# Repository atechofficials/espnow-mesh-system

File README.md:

# ESPNow Mesh System

A local-first ESP32 smart-home system for **wireless sensing and control**.

This project lets you build a small home mesh using **ESP32-based nodes** and a central **ESP32-S3 gateway**.  
The gateway connects to your Wi-Fi, hosts a browser-based dashboard, can optionally expose its own built-in **SPI room sensor with runtime BMP280/BME280 auto-detection**, communicates with nearby nodes over **ESP-NOW**, can fall back to its own **Offline Mode AP** when your router is unavailable, optionally bridges the system to a local **MQTT broker**, publishes **Home Assistant MQTT auto-discovery**, and uses a companion **ESP32-C3 coprocessor** to handle **gateway-managed Node OTA updates** and future helper tasks.

That means you can:

- monitor room conditions like temperature, humidity, pressure, and light
- use the gateway by itself with an optional built-in room sensor before you add wireless nodes
- control actuator devices like relays from a web dashboard
- mirror supported devices and controls into Home Assistant through MQTT auto-discovery
- pair nodes without entering Wi-Fi credentials on each node
- keep everything running on your own local network

No cloud account. No subscription. No internet dependency for normal use.

---

## What This Project Can Do

### Live monitoring
Open the gateway's IP address in your browser to view live sensor readings from all paired nodes.

### Local control
Turn relays on and off directly from the dashboard.

### Easy pairing
Put a node into pairing mode and the gateway can discover and register it automatically. Fresh, unrenamed nodes now advertise with the last 4 characters of their MAC address appended to the default node name, making it easier to tell identical boards apart before you rename them from the dashboard. The current release line also tightens beacon/discovery timing so pairing candidates appear faster and stale "available to pair" entries clear sooner after a node powers down.

### Node settings from the browser
Change node settings such as:
- Status LED enable/disable
- Relay state persistence
- Sensor-specific options

### Gateway-managed Node OTA
Upload compatible sensor-node, actuator-node, or hybrid-node firmware from the gateway web interface and let the gateway update the selected node without connecting that node to your home Wi-Fi. The gateway now validates both the node role and the node hardware configuration ID before delivery begins.

### Offline gateway access
If your router is unavailable, the gateway can now switch to an **ESP32-S3-hosted Offline Mode AP** so the dashboard stays reachable without internet or home-network access. You can also choose manual offline mode during setup and edit the offline AP credentials later from the dashboard.

### MQTT and Home Assistant
If you enable MQTT in the gateway settings, the gateway publishes **Home Assistant MQTT discovery** for itself, its optional built-in sensor, and supported paired nodes. Relay controls, supported node settings, reboot/unpair actions, and gateway reboot/factory-reset actions can then be used from Home Assistant while staying synchronized with the gateway dashboard.

For temperature reporting, the gateway publishes MQTT temperatures in **degrees Celsius only** for both the built-in sensor and paired sensor nodes. Temperature-unit controls are intentionally **not** exposed to Home Assistant because Home Assistant already handles user-side Celsius/Fahrenheit conversion.

### Automatic recovery
If the gateway or node reboots, the system reconnects automatically and restores state where supported.

---

## Current Project Status

The project already supports **sensor nodes**, **actuator nodes**, and **hybrid nodes**.

### Available right now

| Type | Device | Status |
|------|--------|--------|
| Gateway | ESP32-S3 Gateway | Working |
| Gateway Helper | ESP32-C3 Coprocessor | Working |
| Sensor Node | Envo Mini v1 | Working |
| Actuator Node | ESP32 Relay Node v1 | Working |
| Hybrid Node | ESP32 Hybrid Relay Node v1 | Working |

### Current node capabilities

**Envo Mini v1**
- Temperature
- Atmospheric pressure
- Humidity
- Ambient light

**ESP32 Relay Node v1**
- 4 independent relay outputs
- Relay control from dashboard
- Relay state persistence across reboot
- Status LED setting from dashboard

**ESP32 Hybrid Relay Node v1**
- 4 independent relay outputs
- 4 TTP224 touch inputs
- RC522 RFID card reader support
- RFID card actions that apply saved relay scenes
- Relay control, state sync, and RFID management from the dashboard

### Current MQTT capabilities

- Local MQTT bridge from the gateway to a Mosquitto-compatible broker
- Home Assistant MQTT auto-discovery for:
  - the gateway device
  - optional gateway built-in sensor entities
  - supported sensor, actuator, and hybrid node entities
- Relay and supported setting control from Home Assistant with state sync back to the gateway dashboard
- Gateway reboot and gateway factory reset buttons exposed in Home Assistant
- Graceful retained-topic cleanup during gateway factory reset so the gateway and its connected nodes disappear from Home Assistant cleanly

### Current OTA capabilities

- Gateway self-OTA from the browser with gateway hardware-config ID validation
- Gateway-managed coprocessor OTA from the browser with board-specific coprocessor hardware-config ID validation and progress/error reporting
- Gateway-managed OTA for supported sensor nodes with role and hardware-config ID validation
- Gateway-managed OTA for supported actuator nodes with role and hardware-config ID validation
- Gateway OTA and Node OTA now coordinate helper ownership so the ESP32-C3 coprocessor cannot be reserved by conflicting update flows at the same time
- Gateway self-OTA, coprocessor OTA, and Node OTA remain available while the dashboard is being served through the Offline Mode AP

---

## Why ESP-NOW?

Most DIY smart-home systems put every device directly on Wi-Fi.

This project takes a different approach:

- the **gateway** joins your home Wi-Fi
- the **nodes** talk to the gateway using **ESP-NOW**
- nodes do not need your Wi-Fi password
- pairing is simpler for small embedded devices
- the system stays lightweight and local

This makes the setup especially useful for small ESP32 devices that only need to talk to one central controller.

---

## How It Works

```text
Browser
  |
  | Dashboard
  |
ESP32-S3 Gateway
  |
  | ESP-NOW
  |-- Sensor Nodes
  |-- Actuator Nodes
```

The gateway acts as the bridge between:
- your browser over Wi-Fi
- your MQTT broker / Home Assistant over Wi-Fi
- your ESP32 nodes over ESP-NOW

For **Node OTA**, the gateway temporarily hands firmware delivery to the on-board **ESP32-C3 coprocessor**, which stages the selected node firmware, starts a temporary helper access point, and serves the firmware image to the target node while the main gateway continues managing the mesh and dashboard. Incompatible uploads are blocked up front if the firmware markers do not match the selected node role or hardware configuration. While that helper session is active, the dashboard now blocks conflicting Gateway OTA or coprocessor OTA actions and shows a clear **Coprocessor Busy** state until the helper is free again.

If the gateway loses its router Wi-Fi connection, the **ESP32-S3** can now host an operator-facing Offline Mode AP directly while keeping ESP-NOW active on the last known mesh channel. When the router comes back, the gateway scans for the saved SSID, reconnects automatically, and returns the dashboard to the router-assigned IP.

---

## Hardware Used

### Gateway firmware targets
- ESP32-S3-DevKitC-1-N8R8 for bench development and validation
- Seeed Studio XIAO ESP32-S3 on the new THT gateway carrier variants
- Waveshare ESP32-S3-DevKit-C-N8R8 on the new THT gateway carrier variants

### Gateway helper targets
- ESP32-C3 Super Mini
- Seeed Studio XIAO ESP32-C3
- DFRobot Beetle ESP32-C3

### Gateway reference PCB variants

The current gateway hardware release line now consists of four single-layer, thick-trace, THT-friendly PCB variants intended to be easy to hand-fabricate at home:

| Variant | Main MCU board | Helper MCU board |
|---------|----------------|------------------|
| `ESP32_Mesh_Gateway_v1A` | Seeed Studio XIAO ESP32-S3 | ESP32-C3 Super Mini |
| `ESP32_Mesh_Gateway_v1B` | Seeed Studio XIAO ESP32-S3 | Seeed Studio XIAO ESP32-C3 |
| `ESP32_Mesh_Gateway_v1C` | Seeed Studio XIAO ESP32-S3 | DFRobot Beetle ESP32-C3 |
| `ESP32_Mesh_Gateway_v1D` | Waveshare ESP32-S3-DevKit-C-N8R8 | ESP32-C3 Super Mini |

Shared board-level notes for all four variants:
- All four variants provide solder pads for an optional built-in **BMP280** or **BME280** gateway room sensor module, and the gateway auto-detects which one is attached at boot
- All four variants are intentionally kept on a single copper layer with thick traces for easier home fabrication
- The earlier ESP32-S3 Super Mini based gateway carrier should now be considered deprecated because that board's 4 MB flash is not suitable for the current gateway firmware line, which expects an 8 MB class ESP32-S3 target

### Sensor node reference boards
- DFRobot FireBeetle 2 ESP32-E
- ESP32-C3 Super Mini based **Envo Mini v1** prototype hardware

### Sensor node reference sensors
- BMP280
- DHT22
- TEMT6000

### Actuator node reference board
- ESP32 Dev Module

### Actuator node reference output
- 4-channel active-LOW relay module

### Hybrid node reference add-ons
- TTP224 4-way touch sensor
- RC522 RFID reader module

---

## Quick Start

Board and wiring selection for the current release line are handled through the documented **PlatformIO environments** for each firmware target, with guarded defaults and invalid-define correction in each project's `include/user_config.h`.

### 1. Flash the gateway
Start with the gateway firmware:

[`esp32-gateway/gateway_v1/README.md`](esp32-gateway/gateway_v1/README.md)

For **Node OTA** support, also flash the ESP32-C3 gateway coprocessor once from:

[`esp32-gateway/gateway_v1/coprocessor_esp32c3/`](esp32-gateway/gateway_v1/coprocessor_esp32c3/)

The **Gateway Firmware Update** section in the dashboard can now target either the ESP32-S3 **Main MCU** or the ESP32-C3 **Coprocessor**.

### 2. Flash a node
Choose one:

Sensor node:
[`esp32-nodes/sensor_nodes/envo_mini_v1/README.md`](esp32-nodes/sensor_nodes/envo_mini_v1/README.md)

Actuator node:
[`esp32-nodes/actuator_nodes/esp32_relay_node_v1/README.md`](esp32-nodes/actuator_nodes/esp32_relay_node_v1/README.md)

Hybrid node:
[`esp32-nodes/hybrid_nodes/esp32_hybrid_relay_node_v1/README.md`](esp32-nodes/hybrid_nodes/esp32_hybrid_relay_node_v1/README.md)

### 3. Power on the gateway
On first boot, the gateway opens the setup portal so you can either connect it to your home Wi-Fi or choose manual offline mode with the built-in Offline Mode AP credentials.

### 4. Pair a node
Put a node into pairing mode and let the gateway detect it.

### 5. Open the dashboard
Visit the gateway IP in your browser and start using the system. If the gateway is running in Offline Mode, open:

```text
http://192.168.8.1/
```

### 6. Optional: enable MQTT
If you want Home Assistant integration, open the gateway dashboard, go to the MQTT settings section, enter your broker details, and enable the MQTT bridge. The gateway will publish Home Assistant discovery automatically once it connects to the broker.

---

## Web Dashboard Features

The current dashboard supports:

- viewing all paired nodes
- seeing live sensor readings
- viewing the optional gateway built-in sensor separately from paired-node cards
- controlling relay outputs
- managing Hybrid-node RFID card actions
- opening node settings
- renaming nodes
- rebooting nodes remotely
- updating supported nodes with Node OTA
- updating the gateway main MCU or the ESP32-C3 coprocessor from the **Gateway Firmware Update** section
- disconnecting nodes
- changing gateway settings
- editing built-in gateway sensor temperature-unit / altitude settings when that feature is enabled
- configuring the MQTT bridge and Home Assistant discovery publishing
- editing Offline Mode AP settings and viewing current network mode / access IP
- launching Wi-Fi setup mode
- factory reset options, including a physical long-press reset button on the gateway and graceful node unpairing before the gateway wipes its own state

Home Assistant intentionally does **not** expose:
- relay label settings for actuator or hybrid nodes, because Home Assistant already lets users rename switches and buttons locally
- node or gateway temperature-unit settings, because MQTT temperatures are published in Celsius and Home Assistant handles conversion itself

The dashboard is served directly by the gateway itself.

---

## Who This Project Is For

This project is useful if you are:

### A maker or hobbyist
You want a local smart-home system without cloud dependency.

### A student or learner
You want to explore ESP32 networking, embedded firmware, and browser-based control panels.

### A developer
You want a modular ESP32 project with:
- gateway firmware
- sensor firmware
- actuator firmware
- hybrid node firmware
- a shared protocol
- a live dashboard
- room for future expansion

---

## For Developers

The project is already structured for further development.

If you want to:
- add new sensor nodes
- add new actuator nodes
- add new hybrid nodes
- improve the gateway
- improve the dashboard
- extend the protocol
- contribute fixes or new features

start here:

[`CONTRIBUTING.md`](CONTRIBUTING.md)

More detailed documentation is available in the subproject README files.

---

## Repository Layout

```text
espnow-mesh-system/
|-- README.md
|-- CONTRIBUTING.md
|-- esp32-gateway/
|-- esp32-nodes/
|-- docs/
```

### Main sections

- [`esp32-gateway/`](esp32-gateway/)  
  Gateway documentation and firmware
- [`esp32-gateway/gateway_v1/hardware/`](esp32-gateway/gateway_v1/hardware/)  
  Gateway v1A-v1D PCB resources, schematic PDFs, and development references

- [`esp32-nodes/`](esp32-nodes/)  
  Sensor, actuator, and hybrid node firmware

---

## Documentation Map

If you're just exploring:

- Gateway overview: [`esp32-gateway/README.md`](esp32-gateway/README.md)
- Nodes overview: [`esp32-nodes/README.md`](esp32-nodes/README.md)

If you're building hardware:

- Gateway firmware guide: [`esp32-gateway/gateway_v1/README.md`](esp32-gateway/gateway_v1/README.md)
- Gateway v1A-v1D PCB resources: [`esp32-gateway/gateway_v1/hardware/`](esp32-gateway/gateway_v1/hardware/)
- Sensor node guide: [`esp32-nodes/sensor_nodes/envo_mini_v1/README.md`](esp32-nodes/sensor_nodes/envo_mini_v1/README.md)
- Relay node guide: [`esp32-nodes/actuator_nodes/esp32_relay_node_v1/README.md`](esp32-nodes/actuator_nodes/esp32_relay_node_v1/README.md)
- Hybrid node guide: [`esp32-nodes/hybrid_nodes/esp32_hybrid_relay_node_v1/README.md`](esp32-nodes/hybrid_nodes/esp32_hybrid_relay_node_v1/README.md)
- ESP32-C3 Super Mini WiFi test report: [`docs/esp32_c3_supermini_wifi_tests/README.md`](docs/esp32_c3_supermini_wifi_tests/README.md)

If you're contributing code:

- Contribution guide: [`CONTRIBUTING.md`](CONTRIBUTING.md)

---

## Project Direction

The project currently supports:
- local sensor monitoring
- local relay control
- local RFID-driven relay scenes on Hybrid nodes
- browser-based node management
- gateway-managed Node OTA for supported sensor, actuator, and hybrid nodes with role and hardware-config safety checks
- board-specific configuration cleanup through the new `user_config.h` release line for gateway and node firmware
- ESP32-C3 Super Mini board support with board-gated WiFi transmit power limiting on node firmware where needed

Planned future growth may include:
- more sensor node types
- more actuator node types
- more hybrid sensor + actuator nodes
- improved dashboard views and charts
- cleaner onboarding and flashing experience

---

## License

MIT License

See [`LICENSE`](LICENSE)

---

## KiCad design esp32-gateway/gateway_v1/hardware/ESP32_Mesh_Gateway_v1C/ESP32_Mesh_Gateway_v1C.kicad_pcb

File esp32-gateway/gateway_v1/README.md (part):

# Gateway v1 - Build, Flash, and OTA Guide

Firmware version: **2.6.7**  
Target board: `esp32-s3-devkitc1-n8r8`

Gateway helper coprocessor: **ESP32-C3 firmware v0.3.1**

---

## Highlights in v2.6.7
- Adds clearer built-in sensor probe and diagnosis logging in the gateway serial output
- Auto-detects whether the connected built-in SPI sensor is **BMP280** or **BME280** at runtime and shows data accordingly
- Removes the old manual built-in sensor type selection logic and keeps only a simple built-in sensor enable flag

## Highlights in v2.6.4
- Adds an optional **MQTT bridge** from the gateway to a local broker using `PubSubClient`
- Adds **Home Assistant MQTT auto-discovery** for the gateway, optional gateway built-in sensor, and supported paired sensor/actuator/hybrid nodes
- Keeps supported controls synchronized between Home Assistant and the gateway dashboard
- Exposes **Gateway Reboot** and **Gateway Factory Reset** as Home Assistant MQTT buttons
- Clears retained MQTT discovery/state topics during gateway factory reset so the gateway and its connected nodes disappear cleanly from Home Assistant
- Keeps MQTT temperature publishing in **degrees Celsius only** and intentionally leaves temperature-unit conversion to Home Assistant

## Highlights in v2.5.0
- Adds optional gateway built-in **BMP280/BME280** sensor support on the dedicated gateway PCB header/pads
- Adds a dedicated **Gateway Built-in Sensor** dashboard card plus Settings-page controls for temperature unit and altitude reference
- Keeps the built-in sensor separate from paired-node management and shows a clear Sensor not detected state when the feature is enabled but the hardware is missing or faulty
- Keeps the optional built-in sensor feature board-gated while moving BMP280/BME280 model selection to runtime auto-detection in the newer release line
- Hardens **ESP32-C3 Super Mini** helper AP behavior for Node OTA by applying the documented **8.5 dBm** Wi-Fi TX power cap after Wi-Fi startup and preserving helper-side Wi-Fi stability safeguards
- Refines gateway-side Node OTA status wording so accepted OTA requests report that the gateway is waiting for the node to connect to the helper AP

## Highlights in v2.4.1
- Updates the gateway factory reset flow so all currently paired nodes receive an explicit `UNPAIR_CMD` before the gateway wipes its own state
- Applies this graceful node disconnect behavior to both reset entry points:
  - dashboard **Factory Reset**
  - physical reset button hold sequence
- Prevents previously paired nodes from treating gateway factory reset like a temporary gateway reboot
- Leaves nodes in their expected unpaired / pairing-ready state after factory reset so they can be paired again cleanly
- Uses each node's actual node type in the unpair command path instead of stamping every unpair as `NODE_SENSOR`

## Highlights in v2.4.0
- Adds **Gateway Offline Mode** hosted directly on the ESP32-S3 so the dashboard remains reachable even when the home router is unavailable
- Adds setup-portal controls for choosing **manual Offline Mode** and editing the dedicated Offline Mode AP credentials
- Automatically falls back from router STA mode to the Offline Mode AP when the saved router link is lost
- Automatically scans for the saved router SSID and returns from Offline Mode back to normal router STA mode when that network comes back
- Keeps **Gateway OTA**, **Coprocessor OTA**, and **Node OTA** functional while the gateway is being accessed through the Offline Mode AP
- Adds reconnect-aware dashboard notifications so users are told when the gateway loses the router, switches to Offline Mode, and later returns to router mode
- Adds a runtime **physical factory reset** flow using the board-specific `RESET_BTN_PIN` from `include/user_config.h` instead of relying only on the dashboard action
- Adds a dedicated RGB LED reset sequence for physical factory reset:
  - blinking dark orange while the button is being held
  - solid red once the reset hold threshold is reached
- Increases the physical reset hold time to **6 seconds** for clearer visual confirmation

## Highlights in v2.3.1
- Hardens OTA coordination so **Node OTA**, **Gateway OTA**, and **coprocessor OTA** cannot reserve the ESP32-C3 helper at the same time
- Shows **Coprocessor Busy. Please try after some time.** across the dashboard when the helper is already occupied, including both **Main MCU** and **Coprocessor** targets in the **Gateway Firmware Update** section
- Fixes the Node OTA helper upload-begin target so staged node firmware reaches the coprocessor helper correctly again
- Clears stale Node OTA and coprocessor OTA panel state automatically after backend cleanup so the dashboard returns to idle cleanly

## Highlights in v2.3.0
- Adds **ESP32-C3 coprocessor OTA** support through the **Gateway Firmware Update** section in the web dashboard
- Adds a target selector in the dashboard so the **Gateway Firmware Update** flow can address either the ESP32-S3 **Main MCU** or the ESP32-C3 **Coprocessor**
- Adds board-specific coprocessor firmware validation using the helper board hardware-config ID before UART OTA transfer begins
- Improves OTA error reporting so firmware mismatch messages include the uploaded hardware-config ID clearly in both the serial logs and the web UI
- Adds explicit PlatformIO build environments for the documented gateway hardware combinations and the current custom development combo

## Highlights in v2.2.0
- Polishes discovery timing on both the gateway and node side so pairing candidates appear faster and stale entries clear sooner
- Introduces the `user_config.h` configuration split for cleaner user-tunable firmware definitions
- Documents the current gateway hardware release line around four valid THT-friendly PCB variants (`v1A` to `v1D`)
- Keeps the ESP32-C3 helper workflow aligned with the newer `v0.3.1` coprocessor firmware line

## Highlights in v2.1.4
- Increased the shared node-name field from 16 bytes to 25 bytes (24 visible characters + NUL) for beacon and registration messages, enabling clearer default node names, MAC-suffixed first-boot node names, and longer user-defined names while remaining well within ESP-NOW payload limits

## Highlights in v2.1.3

- Adds a gateway-side **max node capacity** check before a new pairing flow is started
- Shows a dismissible dashboard popup when the user tries to connect another node after the gateway is already full
- Re-shows the capacity warning on repeated over-limit pairing attempts instead of silently failing
- Hardens gateway node-registry restore so temporary low-`MESH_MAX_NODES` test builds do not corrupt runtime memory on boot
- Continues support for the current **ESP32-C3 gateway coprocessor**, Hybrid-node handling, RFID dashboard flow, gateway OTA, and gateway-managed Node OTA

## Highlights in v2.1.2

- Adds the first **ESP32 Mesh System Gateway v1.0A** hardware release to the repository under `hardware/`
- Documents a home-fabrication-friendly gateway PCB built around off-the-shelf **ESP32-S3 Super Mini** and **ESP32-C3 Super Mini** development boards
- Aligns the documented ESP32-S3 <-> ESP32-C3 UART wiring with the new PCB layout:
  - **ESP32-S3 TX GPIO4 -> ESP32-C3 RX GPIO0**
  - **ESP32-S3 RX GPIO5 -> ESP32-C3 TX GPIO1**
- Continues the current gateway OTA, Node OTA, Hybrid-node, and mobile-web-UI feature set from the v2.1.1 release line

## Highlights in v2.1.1

- Continues the **gateway-managed Node OTA** workflow for supported sensor, actuator, and hybrid nodes
- Continues first-class **Hybrid node** handling with capability-aware actuator/RFID synchronization
- Continues support for the **ESP32 Hybrid Relay Node v1** and its RFID card-action workflow in the dashboard
- Adds RFID scan toasts in the dashboard for **new card detection** and **known card action execution**
- Improves the **mobile web UI** with better top-bar responsiveness, mobile sidebar gateway actions, and improved side-nav behavior in portrait and landscape orientations
- Replaces the browser reboot confirmation with a custom **Reboot Gateway** popup consistent with the Factory Reset flow
- Improves popup styling, warning-icon visibility, small-screen landscape fit, and background scroll locking for side menus and dialogs
- Preserves actuator state across gateway reboot so relay cards recover correctly after restart
- Improves gateway OTA success/reboot feedback in the web interface
- Continues support for the **ESP32-C3 gateway coprocessor**, `coproc_ota_protocol.h`, gateway web credentials, relay label assignment, gateway LED control, and schema-driven node settings

---

## Prerequisites

- [PlatformIO Core](https://docs.platformio.org/en/latest/core/installation/index.html) or the PlatformIO IDE extension for VS Code
- USB cable connected to the selected ESP32-S3 gateway main board
- USB cable connected to the selected ESP32-C3 coprocessor board when flashing or debugging the helper firmware

The current hardware release line in `hardware/` instead targets four single-layer carrier-PCB variants built around off-the-shelf ESP32-S3 and ESP32-C3 development boards.

---

## Gateway Hardware Release Line

The current gateway PCB release line documents four valid single-layer, thick-trace, home-fabrication-friendly variants:

| Variant | Main MCU board | Helper MCU board |
|---------|----------------|------------------|
| `ESP32_Mesh_Gateway_v1A` | Seeed Studio XIAO ESP32-S3 | ESP32-C3 Super Mini |
| `ESP32_Mesh_Gateway_v1B` | Seeed Studio XIAO ESP32-S3 | Seeed Studio XIAO ESP32-C3 |
| `ESP32_Mesh_Gateway_v1C` | Seeed Studio XIAO ESP32-S3 | DFRobot Beetle ESP32-C3 |
| `ESP32_Mesh_Gateway_v1D` | Waveshare ESP32-S3-DevKit-C-N8R8 | ESP32-C3 Super Mini |

Shared board-level notes:

- all four variants keep solder pads for an optional **BMP280** or **BME280** gateway-side built-in sensor module
- all four variants are intentionally laid out on a single copper layer with thick traces for easier home fabrication
- the earlier ESP32-S3 Super Mini based gateway carrier should now be treated as deprecated because that board only has 4 MB flash and is not suitable for the current gateway firmware line

The same `hardware/` tree also includes schematic PDFs and a `Development_Resources/` folder with dev-board pinouts and MCU reference documents.

---

## PlatformIO Build Environments

The gateway release line now exposes explicit build environments in `platformio.ini` so users can build the correct firmware for each documented hardware combination without editing board macros manually.

| Environment | Main MCU board | Coprocessor board |
|-------------|----------------|-------------------|
| `gateway_v1a` | Seeed Studio XIAO ESP32-S3 | ESP32-C3 Super Mini |
| `gateway_v1b` | Seeed Studio XIAO ESP32-S3 | Seeed Studio XIAO ESP32-C3 |
| `gateway_v1c` | Seeed Studio XIAO ESP32-S3 | DFRobot Beetle ESP32-C3 |
| `gateway_v1d` | Waveshare ESP32-S3-DevKit-C-N8R8 | ESP32-C3 Super Mini |
| `development` | Espressif ESP32-S3-DevKitC-1-N8R8 | DFRobot Beetle ESP32-C3 |

When building or uploading from USB, select the environment that matches the actual gateway hardware pair you are using.

The current release line keeps the optional gateway built-in sensor feature behind `GATEWAY_BUILTIN_SENSOR_ENABLED`, and the firmware auto-detects whether the attached SPI module is BMP280 or BME280 at runtime.

The newer release line also keeps board and helper selection in PlatformIO build environments while `include/user_config.h` provides guarded defaults and invalid-define correction when no explicit board combination is selected.
## Dependencies

Managed automatically by PlatformIO via `platformio.ini`:

| Library | Version |
|---------|---------|
| WiFiManager | 2.0.17 |
| ESPAsyncWebServer | 3.6.0 |
| AsyncTCP | 3.3.2 |
| ArduinoJson | 7.4.3 |
| Adafruit NeoPixel | 1.15.4 |
| Adafruit Unified Sensor | 1.1.15 |
| Adafruit BMP280 Library | 2.6.8 |
| Adafruit BME280 Library | 2.3.0 |
| PubSubClient | 2.8 |

Framework libraries used directly (no extra install needed): `LittleFS`, `Preferences`, `WiFi`, `esp_now`, `Update`.

---

## Partition Layout

The project now builds against **`partitions_8mb_ota.csv`**.

| Partition | Size |
|-----------|------|
| `nvs` | 20 KB |
| `otadata` | 8 KB |
| `app0` | 1792 KB |
| `app1` | 1792 KB |
| `LittleFS` | 4544 KB |
| `coredump` | 64 KB |

This layout is required for the web-based Gateway OTA update feature and leaves the gateway firmware on an OTA-capable base while the ESP32-C3 helper handles node-firmware delivery.

---

## First-Time Flash / Migration to the OTA-Capable Gateway Line

If you are coming from an older gateway build that used the non-OTA partition table, the **first upgrade to the current OTA-capable gateway line must be done over USB**.

Run these commands from the `gateway_v1/` directory:

```bash
# 1. Erase flash for a clean migration
pio run --target erase

# 2. Upload the LittleFS web assets
pio run --target uploadfs

# 3. Compile and upload the firmware
pio run --target upload
```

After this migration, future **gateway firmware** updates can be done from the web interface.

To use **Node OTA**, also flash the ESP32-C3 helper once from the `coprocessor_esp32c3/` directory:

```bash
cd coprocessor_esp32c3
pio run --target erase
pio run --target upload
pio device monitor
```

See [coprocessor_esp32c3/README.md](coprocessor_esp32c3/README.md) for the helper-specific hardware, transport, and runtime details.

If you change only the dashboard assets later, run:

```bash
pio run --target uploadfs
```

If you change only the firmware later and want to use USB instead of OTA, run:

```bash
pio run --target upload
```

---

## ESP32-C3 Gateway Coprocessor

The Node OTA workflow uses a dedicated **ESP32-C3 coprocessor** connected to the ESP32-S3 gateway.

During a node update, the gateway:

1. validates and stages the uploaded node `firmware.bin`
2. transfers that firmware to the ESP32-C3 helper over UART
3. tells the helper to start a temporary OTA access point
4. instructs the selected node to join that helper AP
5. waits for the node to download, flash, reboot, and re-register

The coprocessor also reports OTA helper status back to the gateway so the web interface can show live progress.

The exact UART routing depends on the selected gateway PCB variant and helper dev board. Keep the helper UART definitions in sync with the intended hardware pair and document any board-specific differences in the hardware release notes when they change.

Shared transport definitions between the gateway and helper live in:

- `include/coproc_ota_protocol.h`
- `coprocessor_esp32c3/include/coproc_ota_protocol.h`

Keep those copies synchronized.

---

## First Boot

1. The gateway tries to reconnect to saved Wi-Fi credentials automatically
2. If no router credentials are stored, WiFiManager opens the setup portal AP:
   - SSID: **`ESP32-Mesh-Gateway`**
   - Password: **`meshsetup`**
3. Connect to that AP from a phone or laptop
4. Open the captive portal and either:
   - select and save your home Wi-Fi network, or
   - enable **Manual Offline Mode** so the gateway boots directly into its dedicated Offline Mode AP
5. After connection to your router, the dashboard becomes available at:

```text
http://<gateway-ip>/
```

6. If the gateway is running in Offline Mode instead, the dashboard becomes available at:

```text
http://192.168.8.1/
```

Wi-Fi credentials, gateway settings, and paired-node records are stored in NVS and survive reboot.

---

## Gateway Offline Mode

The current gateway release line supports a dedicated **Offline Mode AP** hosted on the ESP32-S3 main MCU.

This mode is intended for cases where:

- the gateway has not been given router credentials yet
- the user explicitly enables **Manual Offline Mode** from the setup portal
- the saved home router disappears and the gateway must remain reachable locally

### Offline Mode behavior

- the gateway starts the dedicated Offline Mode AP with its own SSID/password
- the dashboard is served from **`http://192.168.8.1/`**
- paired nodes stay available over ESP-NOW on the last active mesh channel
- the gateway keeps retrying for the saved router SSID in the background
- once the saved router becomes visible again, the gateway automatically returns to normal online router mode

### Configuration

- Offline Mode AP credentials can be changed from the setup portal and later from the dashboard
- setup-portal credentials and Offline Mode AP credentials are stored separately
- router credentials are also mirrored into gateway config storage so reconnect and failover behavior remains reliable across reboot

---

## Gateway Built-in Sensor

The current gateway release line can optionally expose a gateway-side **BMP280** or **BME280** module soldered to the built-in sensor pads on the PCB.

### Configuration

- the built-in sensor feature is enabled or disabled with `GATEWAY_BUILTIN_SENSOR_ENABLED`
- when enabled, the gateway probes the attached SPI module at boot and auto-detects whether it is a BMP280 or BME280
- the gateway reuses the board-specific SPI pin mapping defined in `user_config.h` and prints clearer serial probe diagnostics when detection succeeds or fails

### Dashboard and Settings behavior

- the dashboard shows a dedicated **Gateway Built-in Sensor** card instead of treating the sensor like a paired node
- temperature and sea-level-corrected pressure are shown for both detected BMP280 and BME280 modules
- the built-in sensor status badge reflects the detected model (`BMP280` or `BME280`)
- humidity is shown only when the detected module is BME280
- the Settings page exposes temperature-unit and altitude-reference controls for the built-in sensor
- if the feature is enabled in firmware but the module is missing or faulty, the dashboard and Settings page remain visible and report **Sensor not detected**
- the MQTT / Home Assistant bridge publishes gateway built-in temperature in **degrees Celsius only** and does not expose the built-in sensor temperature-unit setting, because Home Assistant already handles unit conversion on its own side

---

## MQTT and Home Assistant Integration

The current gateway release line can optionally bridge the local ESP-NOW system into a Mosquitto-compatible MQTT broker.

When MQTT is enabled from the dashboard:

- the gateway publishes Home Assistant MQTT discovery automatically
- the gateway itself appears as a Home Assistant device
- supported paired nodes appear under the same gateway-managed device hierarchy
- relay controls, supported node settings, reboot actions, and unpair actions can be triggered from Home Assistant
- gateway reboot and factory reset can also be triggered from Home Assistant

Intentional Home Assistant behavior:

- relay label settings are **not** exposed, because Home Assistant already lets users rename switches/buttons locally
- temperature-unit settings are **not** exposed for the gateway built-in sensor or paired sensor nodes
- MQTT temperatures are published in **degrees Celsius** only, and Home Assistant handles conversion to Fahrenheit if the user selects that display unit

During gateway factory reset, the firmware now clears retained MQTT discovery/state topics before rebooting so the gateway and its connected nodes disappear from Home Assistant cleanly instead of leaving stale devices behind.

---

## Gateway OTA Update from the Web Interface

Once an OTA-capable gateway build is already installed, the gateway can update its **own firmware** directly from the dashboard.

This flow remains available when the dashboard is being served either from the normal router connection or from the ESP32-S3 Offline Mode AP.

### Steps

1. Build a new gateway firmware binary:

```bash
pio run
```

2. Open the dashboard in a browser
3. Go to **Settings -> Gateway Firmware Update**
4. Select the new `firmware.bin`
5. Click **Upload Gateway Firmware**
6. Confirm the update when prompted

The **Gateway Firmware Update** panel now includes a target selector with **Main MCU** and **Coprocessor** options. The steps in this section cover the ESP32-S3 main-firmware path.
### What the gateway does

- validates the uploaded image
- validates the uploaded gateway hardware configuration marker (`GWHWCFG`)
- checks OTA slot size and image type
- flashes the inactive OTA slot
- reports progress/errors in the web UI
- reboots into the new firmware automatically on success

### Notes

- Upload **`firmware.bin`**, not `bootloader.bin`, not `partitions.bin`
- If the web UI assets were changed, also upload LittleFS via `pio run --target uploadfs`
- The current release line moves user-facing configuration definitions into `user_config.h`; older checkouts may still have some of the same knobs in `src/main.cpp`

---

## Gateway Coprocessor OTA Update from the Web Interface

The same **Gateway Firmware Update** panel can now also update the attached **ESP32-C3 coprocessor** from the browser.

This flow also remains available while the gateway is operating in Offline Mode.

### Steps

1. Build the matching coprocessor helper firmware binary from `coprocessor_esp32c3/` using the correct environment for your helper board
2. Open the dashboard in a browser
3. Go to **Settings -> Gateway Firmware Update**
4. Select **Coprocessor** from the MCU target dropdown
5. Select the helper `firmware.bin`
6. Click **Upload Gateway Firmware**

### What the gateway does

- validates the uploaded ESP32 application image
- validates the uploaded coprocessor hardware-config marker against the expected helper board type
- checks that the image fits in the coprocessor OTA slot
- stages the firmware in LittleFS
- asks the helper to halt normal work and prepare for self-OTA
- transfers the firmware to the ESP32-C3 over UART
- waits for the helper to flash, reboot, and reconnect
- reports progress and errors back to the web UI

### Notes

- Upload the helper `firmware.bin` from the environment matching your helper board: `beetle_esp32c3`, `xiao_esp32c3`, or `esp32c3_sm`
- Wrong-board helper uploads are rejected before UART transfer begins
- If the ESP32-C3 is already serving as the Node OTA helper, the **Gateway Firmware Update** section now blocks both MCU targets and shows a shared **Coprocessor Busy** message until the helper is released
## Node OTA Update from the Web Interface

The gateway can also update a paired **sensor node**, **actuator node**, or **hybrid node** from the dashboard.

This flow remains available in both normal router mode and the ESP32-S3 Offline Mode AP.

### Supported flow

1. Build the target node firmware and locate its `firmware.bin`
2. Open the dashboard in a browser
3. Go to the **Node OTA Update** section
4. Select the target node and upload the matching node `firmware.bin`
5. Wait for the gateway to stage the file, arm the ESP32-C3 helper, and start the temporary helper AP
6. The target node downloads the staged image, flashes it, reboots, and re-registers automatically

### What the gateway checks

- uploaded image role matches the selected node type (`SENSOR`, `ACTUATOR`, or `HYBRID`)
- uploaded node hardware configuration marker matches the selected node's reported `HW_CONFIG_ID`
- firmware metadata is readable before starting delivery
- helper staging finishes successfully on the ESP32-C3
- the node accepts OTA mode and reconnects after reboot

### Notes

- Upload **node `firmware.bin`** from the node project, not bootloader or partition files
- The node does **not** need your home Wi-Fi credentials; it only joins the temporary helper AP for the OTA window
- If the coprocessor is already busy with a helper self-update, the **Node OTA Update** section disables its controls and shows the shared **Coprocessor Busy** message until the helper is available again
- Supported and verified flows now include same-version reflashing, upgrades, downgrades, sensor-node OTA, relay-node OTA, hybrid-node OTA, and node OTA after gateway reboot

---

## Updating the Setup Portal AP Credentials

The WiFiManager setup-portal SSID and password can be changed from the dashboard without reflashing:

1. Open **Settings -> Gateway Network**
2. Edit the setup AP SSID and/or password
3. Click **Save AP Config**

These values are used the next time the gateway has to open the setup portal.

---

## Web Interface Access Control

The dashboard can be left open or protected with username/password credentials from the web interface.

### Stored in NVS

- web username
- password hash
- remember token

If credentials are forgotten, recover access by performing a **factory reset**.

---

## Factory Reset

Hold the dedicated **physical factory reset button** connected to the currently selected `RESET_BTN_PIN` in `include/user_config.h` for **6 seconds** while the gateway is running, or trigger **Factory Reset** from the dashboard.

The exact MCU pin is **board-dependent** and may differ between gateway hardware variants and build environments, so do not assume a universal reset-button pin across all gateway boards.

During a physical reset hold, the gateway RGB LED shows:

- **blinking dark orange** while the reset hold is in progress
- **solid red** once the hold threshold has been reached and reset is about to trigger

If the button is released early, the reset is canceled and LED ownership returns to the previous runtime state.

The physical reset LED sequence is always shown, even if the user has disabled the normal Gateway Status LED from the dashboard.

Before the gateway wipes its own registry and saved credentials, it now sends a graceful unpair/disconnect command to every currently paired node. This allows those nodes to clear their saved gateway binding and return to pairing mode instead of briefly behaving as though the gateway only rebooted temporarily.

This clears:

- saved Wi-Fi / router credentials
- custom setup AP credentials
- custom Offline Mode AP credentials
- web interface credentials
- paired node registry
- saved relay label assignments

The gateway then reboots and returns to setup mode.

---

## Key Configuration (`include/user_config.h`)

The current release line keeps board selection, pin definitions, and user-facing firmware defaults in `include/user_config.h` so `main.cpp` can stay focused on runtime logic. Older checkouts may still keep some of the same constants in `src/main.cpp`.

The newer `v2.4.1` line also keeps the setup-portal defaults, Offline Mode defaults, board-specific reset-button wiring through `RESET_BTN_PIN`, and gateway LED ownership behavior aligned through `user_config.h`.

| Constant | Default | Description |
|----------|---------|-------------|
| `AP_SSID_DEFAULT` | `"ESP32-Mesh-Gateway"` | WiFiManager setup portal SSID |
| `AP_PASS_DEFAULT` | `"meshsetup"` | WiFiManager setup portal password |
| `WEB_PORT` | `80` | HTTP/WebSocket port |
| `WS_UPDATE_MS` | `2000` | Node/discovery push interval to browser |
| `WS_META_MS` | `10000` | Gateway meta push interval to browser |
| `RX_QUEUE_SIZE` | `30` | Incoming ESP-NOW packet queue depth |
| `GW_LED_PIN` | `38` | On-board WS2812B gateway status LED |

Timing constants shared with the nodes live in `include/mesh_protocol.h`.

Node OTA transport and helper constants are shared with the ESP32-C3 helper through `include/coproc_ota_protocol.h`.

Use `user_config.h` for board-specific pin mappings, helper UART routing, and other user-tunable firmware selections in the newer release line.

If you are working against one of the gateway PCB variants instead of the original dev-kit wiring, keep the UART pin assignments and helper-board assumptions aligned with the specific hardware variant you are building.

---

## Serial Monitor

```bash
pio device monitor
```

Default baud rate: **115200**

Useful log prefixes:

| Prefix | Meaning |
|--------|---------|
| `[BOOT]` | Startup sequence |
| `[FS]` | LittleFS mount / file listing |
| `[WiFi]` | Wi-Fi connection events |
| `[ESP-NOW]` | ESP-NOW init and TX callbacks |
| `[DISC]` | Node discovery |
| `[PAIR]` | Pairing handshake |
| `[MESH]` | Node registration, relay/actuator state, reconnects |
| `[CFG]` | Gateway or node configuration activity |
| `[AUTH]` | Web interface authentication |
| `[WS]` | WebSocket client activity |
| `[OTA]` | Gateway OTA upload and reboot flow |
| `[C3]` | ESP32-C3 helper handshake, staging, and helper status |
| `[NODE OTA]` | Node OTA job lifecycle, node reconnect detection, and completion |

---

## WebSocket Message Reference

The dashboard communicates with the gateway over a single WebSocket at:

```text
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
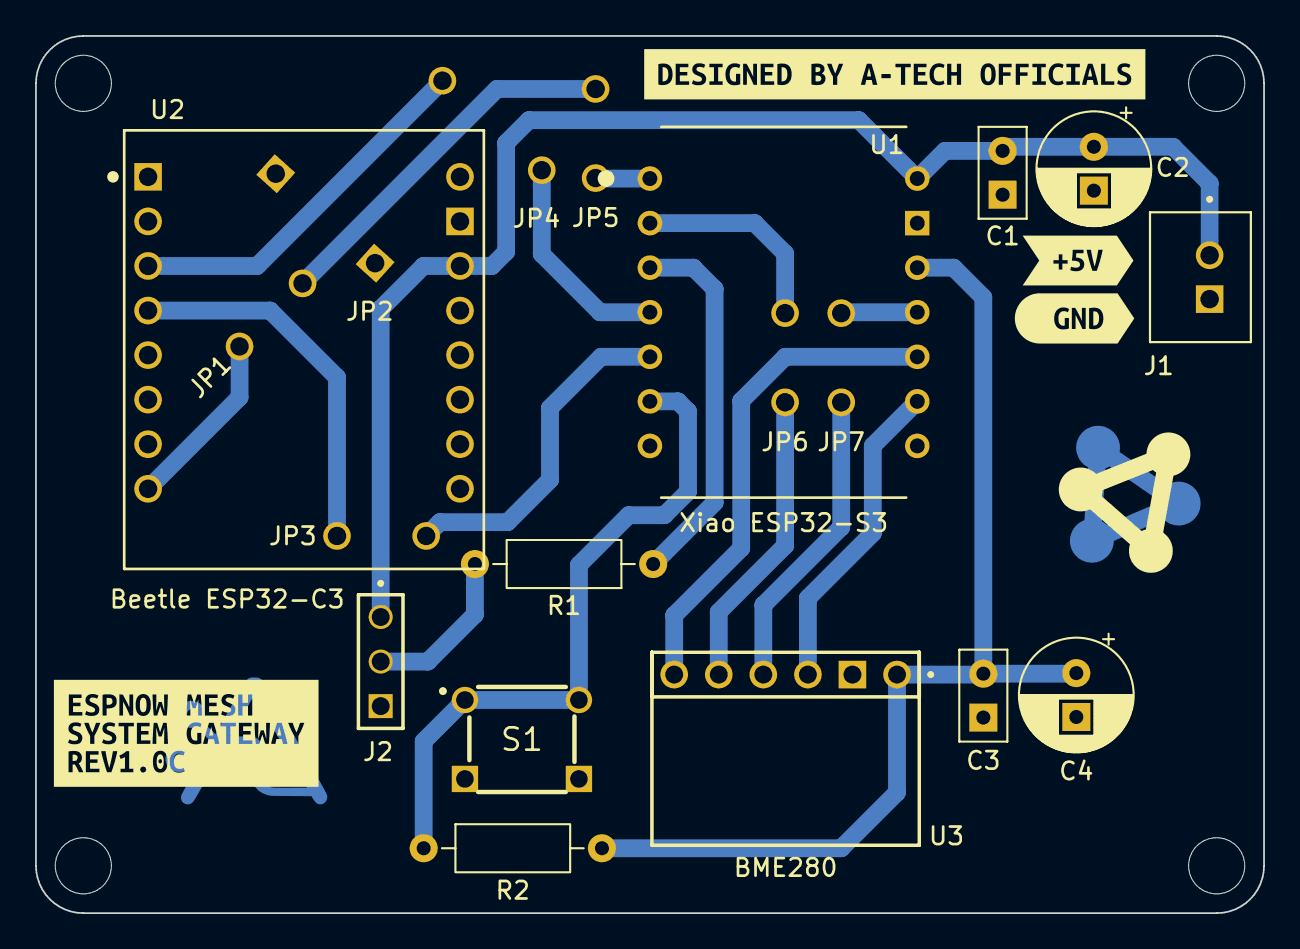
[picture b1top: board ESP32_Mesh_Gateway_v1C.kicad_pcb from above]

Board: 2 copper layers, 70.0 x 50.0 mm, 27 parts (0 on the bottom side), 13 nets.

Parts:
C1, C3: 100nF; C_Disc_D5.0mm_W2.5mm_P2.50mm
C2, C4: 100uF; CP_Radial_D6.3mm_P2.50mm
H1, H2, H3, H4: MountingHole; MountingHole_3.2mm_M3_DIN965
J1: Ext Power; B2B-XH-A__LF__SN_
J2: RGB LED; SAMTEC_TSW-103-07-G-S
JP1, JP3, JP5, JP6, JP7: 2H_Jumper_P5.08mm; 2H_Jumper_P5.08
JP2, JP4: 2H_Jumper_P7.62mm
R1: 100R; R_Axial_DIN0207_L6.3mm_D2.5mm_P10.16mm_Horizontal
R2: 10K; R_Axial_DIN0207_L6.3mm_D2.5mm_P10.16mm_Horizontal
S1: RST BTN; FSM4JH
U1: XIAO-ESP32-S3-DIP; Xiao ESP32-S3 THT
U2: DFRobot Beetle ESP32-C3; DFRobot_Beetle_ESP32-C3
U3: BME280; BME280_Module
kibuzzard-69C035C1: G***; kibuzzard-69C035C1
kibuzzard-69C036F1: G***; kibuzzard-69C036F1
kibuzzard-69C03701: G***; kibuzzard-69C03701
kibuzzard-69CC23E0: G***; kibuzzard-69CC23E0

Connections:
+3.3V: C3.1, C4.1, R2.2, U1.12 (3V3), U3.06
+5V: C1.1, C2.1, J1.1, J2.01, U1.14 (VBUS), U2.14 (VIN)
ARGB_LED: R1.1, U1.3 (GPIO3_A2_D2)
BMP_CS: JP6.1, JP6.2, U1.2 (GPIO2_A1_D1), U3.02
FR_BTN: R2.1, S1.1, S1.2, U1.6 (GPIO6_A5_D5_SCL)
GND: C1.2, C2.2, C3.2, C4.2, J1.2, J2.03, JP2.1, JP2.2, S1.3, S1.4, U1.13 (GND), U2.1 (GND), U2.15 (GND), U3.05
HELPER_RST: JP1.1, JP1.2, JP5.1, JP5.2, U1.1 (GPIO1_A0_D0), U2.8 (GPIO7/SS)
MISO: U1.10 (GPIO8_A9_D9_MISO), U3.01
MOSI: JP7.1, JP7.2, U1.11 (GPIO9_A10_D10_MOSI), U3.03
unnamed: J2.02, R1.2
RXD0: JP3.1, JP3.2, U1.5 (GPIO5_A4_D4_SDA), U2.4 (GPIO1/ADC1)
RXD1: JP4.1, JP4.2, U1.4 (GPIO4_A3_D3), U2.3 (GPIO0/ADC0)
SCK: U1.9 (GPIO7_A8_D8_SCK), U3.04

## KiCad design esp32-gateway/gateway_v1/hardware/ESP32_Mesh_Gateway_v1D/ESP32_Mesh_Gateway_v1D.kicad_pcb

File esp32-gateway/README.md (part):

# ESP32 Gateway

The gateway is the heart of the ESPNow Mesh System. It runs on an **ESP32-S3** and bridges your Wi-Fi network with the ESP-NOW mesh while serving a live web dashboard, managing paired nodes, optionally exposing a built-in **SPI room sensor with runtime BMP280/BME280 auto-detection**, supporting a local **MQTT bridge** with **Home Assistant MQTT auto-discovery**, supporting **web-based gateway OTA firmware updates**, coordinating **gateway-managed Node OTA updates** for sensor, actuator, and hybrid nodes with a companion **ESP32-C3 coprocessor**, and providing an **Offline Mode AP** so the dashboard stays reachable even when your home router is unavailable.

---

## Hardware

| Item | Detail |
|------|--------|
| Main Board | ESP32-S3-DevKitC-1-N8R8 |
| Companion Helper | ESP32-C3 coprocessor for Node OTA and future helper tasks |
| Flash | 8 MB (Quad) |
| PSRAM | 8 MB (Octal) |
| Status LED | WS2812B on GPIO 38 (on-board) |
| Factory reset button | Board-dependent and configured by `RESET_BTN_PIN` in `gateway_v1/include/user_config.h` |

The current gateway hardware release line now tracks four single-layer, thick-trace, THT-friendly PCB variants under `gateway_v1/hardware/`:

| Variant | Main MCU board | Helper MCU board |
|---------|----------------|------------------|
| `ESP32_Mesh_Gateway_v1A` | Seeed Studio XIAO ESP32-S3 | ESP32-C3 Super Mini |
| `ESP32_Mesh_Gateway_v1B` | Seeed Studio XIAO ESP32-S3 | Seeed Studio XIAO ESP32-C3 |
| `ESP32_Mesh_Gateway_v1C` | Seeed Studio XIAO ESP32-S3 | DFRobot Beetle ESP32-C3 |
| `ESP32_Mesh_Gateway_v1D` | Waveshare ESP32-S3-DevKit-C-N8R8 | ESP32-C3 Super Mini |

All four variants include solder pads for an optional built-in **BMP280** or **BME280** gateway-side room sensor, and the gateway now auto-detects the attached sensor model at runtime. The older ESP32-S3 Super Mini based carrier should now be treated as deprecated because the current gateway firmware line expects an 8 MB class ESP32-S3 target.

---

## Responsibilities

- Connects to your home Wi-Fi using a captive portal (WiFiManager) on first boot or when reconfigured
- Can also run in an **ESP32-S3-hosted Offline Mode AP** with separate offline AP credentials
- Automatically falls back to the Offline Mode AP when the router Wi-Fi link is lost and returns to router mode when the saved router SSID is visible again
- Accepts ESP-NOW registrations from nodes and assigns them IDs
- Receives sensor data, heartbeats, and actuator states from paired nodes
- Optionally probes a gateway-side BMP280/BME280 room sensor over SPI, logs clearer detection diagnostics, auto-detects the sensor model at runtime, and exposes it as a dedicated dashboard card instead of a paired node
- Persists built-in sensor display settings such as temperature unit and altitude reference for sea-level pressure calculation
- Publishes optional MQTT discovery/state topics for the gateway, built-in sensor, and supported paired nodes
- Routes supported Home Assistant / MQTT commands back into the same gateway and node control flow used by the dashboard
- Publishes MQTT temperature data in degrees Celsius for Home Assistant and leaves unit conversion to Home Assistant itself
- Forwards dashboard commands to the correct node (pair, unpair, reboot, actuator toggle, settings change)
- Serves the web dashboard from LittleFS over HTTP/WebSocket
- Stores gateway configuration, web credentials, paired node records, node hardware-config IDs, and relay label assignments in NVS
- Supports **gateway self-OTA** from the web interface with validation, hardware-config ID checking, progress reporting, and automatic reboot
- Coordinates **Gateway OTA**, **coprocessor OTA**, and **Node OTA** so the ESP32-C3 helper cannot be reserved by conflicting update flows at the same time
- Keeps **gateway OTA**, **coprocessor OTA**, and **Node OTA** available while the gateway is serving the dashboard through Offline Mode
- Supports both dashboard-triggered and physical-button-triggered factory reset flows, including graceful node unpairing before reset, and LED feedback during the hold sequence
- Supports **Hybrid nodes** with capability-aware state handling, actuator-schema sync, RFID config sync, and RFID scan-event forwarding to the web UI

---

## LED Status Codes

| Colour / Pattern | Meaning |
|------------------|---------|
| Solid white | Boot sequence in progress |
| Dim blue | Gateway operational |
| Green flash | Activity / success pulse |
| Orange flash | Node disconnect feedback |
| Dark-orange blink | Physical factory reset button is being held |
| Solid red | Factory reset hold threshold reached; reset is being confirmed |
| Off | Gateway LED disabled from the web UI |

The factory-reset LED sequence temporarily overrides the normal gateway LED owner and still appears even if the user has disabled the status LED from the web dashboard.

---

## Firmware Changelog

| Version | Notes |
|---------|-------|
| v1.6.0 | Added per-node dynamic settings, remote reboot support, gateway network config from dashboard, and factory reset support |
| v1.7.1 | Maintenance release with minor bug fixes |
| v1.8.0 | Added schema-driven sensor support, generic sensor reading protocol, and multi-sensor node compatibility |
| v1.8.1 | Added gateway status LED toggle support from the web UI with persistent state |
| v1.8.2 | Added ESP32 actuator-node support and improved actuator pairing/state/settings sync |
| v1.8.3 | Added per-relay label assignment from the web interface for relay nodes |
| v1.9.0 | Added **web-based gateway OTA firmware update**, OTA partition layout, upload validation, progress/error feedback, and automatic reboot after successful flash |
| v2.0.0 | Added **gateway-managed Node OTA** for supported sensor and actuator nodes, introduced the ESP32-C3 gateway coprocessor workflow, added helper-assisted node firmware staging/delivery, and extended OTA progress/reconnect tracking in the dashboard |
| v2.0.1 | Added OTA **hardware configuration ID** checks for both gateway OTA and node OTA, persisted node hardware IDs across gateway reboot, and improved OTA mismatch/error reporting in the serial logs and web UI |
| v2.1.0 | Added first-class **Hybrid node** support, introduced the RFID-enabled Hybrid Relay Node flow, added capability-aware actuator/RFID handling, and improved relay-state restore plus gateway OTA UI feedback after reboot |
| v2.1.1 | Improved the **web dashboard UX** with RFID scan toasts, mobile responsive layout fixes, custom reboot confirmation popup, better popup styling on small screens, overlay scroll-lock fixes, and improved UI asset refresh behavior |
| v2.1.2 | Added documentation/support for the **Gateway v1.0A** PCB release, aligned the gateway-helper UART mapping with the new PCB layout, and kept the gateway firmware line in sync with the latest hardware release |
| v2.1.3 | Added gateway-side max-node pairing-capacity enforcement, added dismissible dashboard feedback when pairing is attempted after the gateway is already full, and hardened node-registry restore so reduced `MESH_MAX_NODES` test builds fail safely instead of corrupting memory |
| v2.1.4 | Increased the shared node-name limit from 15 to 24 visible characters, updated gateway discovery/registry/rename handling for longer node names, added backward-compatible NVS restore support while saving new node records in the expanded-name format, and allowed fresh nodes to appear with MAC-suffixed default names for easier identification before manual rename |
| v2.2.0 | Polished gateway-side discovery timing so available nodes appear and expire more predictably, aligned the release docs with the new Gateway v1A-v1D PCB family, and documents the move toward `user_config.h` for user-facing firmware configuration |
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
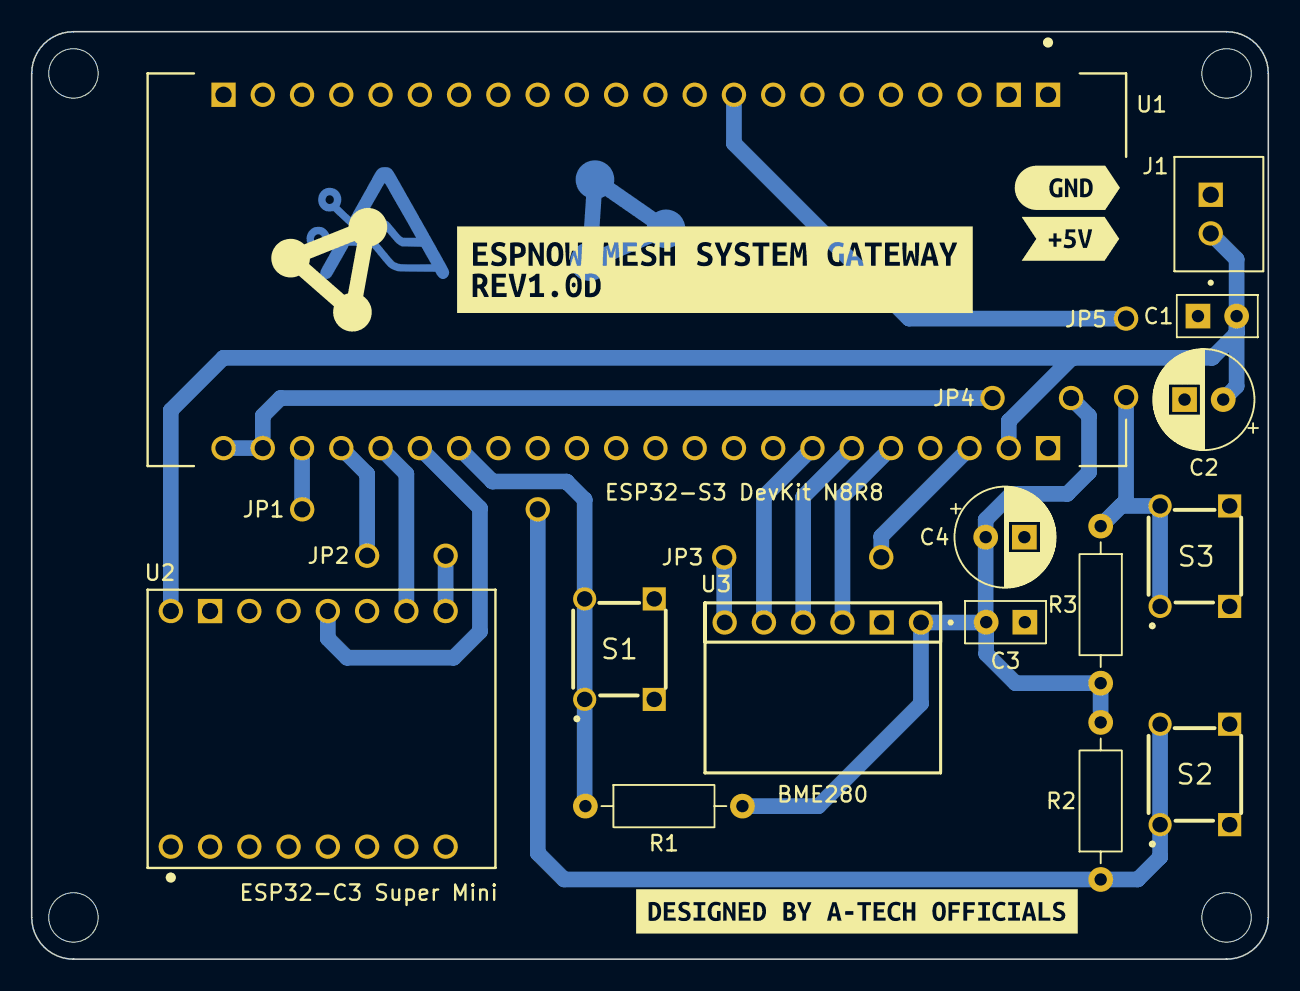
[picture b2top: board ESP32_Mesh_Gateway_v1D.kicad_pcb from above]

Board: 2 copper layers, 80.0 x 60.0 mm, 27 parts (0 on the bottom side), 13 nets.

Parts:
C1, C3: 100nF; C_Disc_D5.0mm_W2.5mm_P2.50mm
C2, C4: 100uF; CP_Radial_D6.3mm_P2.50mm
H1, H2, H3, H4: MountingHole; MountingHole_3.2mm_M3_DIN965
J1: Ext Power; B2B-XH-A__LF__SN_
JP1: 2H_Jumper_P15.24mm
JP2, JP4, JP5: 2H_Jumper_P5.08mm
JP3: 2H_Jumper_P10.16mm
R1, R2, R3: 10K; R_Axial_DIN0207_L6.3mm_D2.5mm_P10.16mm_Horizontal
S1: GW FRST BTN; FSM4JH
S2: MCU RST BTN; FSM4JH
S3: MCU BOOT BTN; FSM4JH
U1: Waveshare ESP32-S3-Dev-Kit-N8R8; Waveshare_ESP32-S3_DevKit_N8R8
U2: ESP32-C3 Super Mini; ESP32-C3_Super_Mini
U3: BME280; BME280_Module
kibuzzard-69C035C1: G***; kibuzzard-69C035C1
kibuzzard-69C036F1: G***; kibuzzard-69C036F1
kibuzzard-69C03701: G***; kibuzzard-69C03701
kibuzzard-69CCEF25: G***; kibuzzard-69CCEF25

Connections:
+3.3V: C3.1, C4.1, JP4.1, JP4.2, R1.2, R2.2, R3.2, U1.23 (3V3), U1.24 (3V3), U3.06
+5V: C1.1, C2.1, J1.1, U1.43 (5V), U2.16 (5V)
BME_CS: U1.38 (SPI1_CS/GPIO10), U3.02
BOOT_BTN: JP5.1, JP5.2, R3.1, S3.1, S3.2, U1.9 (GPIO0/BOOT)
FR_BTN: R1.1, S1.1, S1.2, U1.29 (ADC1_6/GPIO7)
GND: C1.2, C2.2, C3.2, C4.2, J1.2, S1.3, S1.4, S2.3, S2.4, S3.3, S3.4, U1.1 (GND), U1.2 (GND), U1.22 (GND), U1.44 (GND), U2.15 (GND), U3.05
HELPER_RST: U1.28 (ADC1_5/GPIO6), U2.12 (ADC3/GPIO3)
MISO: JP3.1, JP3.2, U1.42 (SPI1_MISO/GPIO14), U3.01
MOSI: U1.39 (SPI1_MOSI/GPIO11), U3.03
RST_BTN: JP1.1, JP1.2, R2.1, S2.1, S2.2, U1.25 (RST)
RXD0: U1.27 (ADC1_4/GPIO5), U2.10 (ADC1/GPIO1)
RXD1: JP2.1, JP2.2, U1.26 (ADC1_3/GPIO4), U2.9 (ADC0/GPIO0)
SCK: U1.40 (SPI1_SCK/GPIO12), U3.04

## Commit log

2026-03-12 feat: initial release of ESPNow Mesh System v1.0
    - ESP32-S3 gateway with WiFiManager, AsyncWebServer, WebSocket dashboard
    - Envo Mini v1 sensor node with ESP-NOW pairing and heartbeat
    - Per-node dynamic settings (temp unit, send interval, LED enable)
    - Schema-on-wire design: nodes self-describe settings to gateway
    - Remote node reboot, rename, disconnect from dashboard
    - Gateway Wi-Fi config and factory reset from dashboard
2026-03-12 feat: add web interface authentication and fix node persistence
    Firmware (main.cpp v1.7.1)
    - Add SHA-256 password hashing with NVS-persisted credentials (gwauth namespace)
    - Add session token and Remember Me token system for stateless HTTP/WS auth
    - Add /api/login, /api/logout, /api/auth_check endpoints with HttpOnly cookie support
    - Add manual Cookie header parsing for ESPAsyncWebServer v3.x compatibility
    - Add WebSocket auth gate: clients must authenticate before receiving any data
2026-03-13 feat: schema-driven sensor system + multi-sensor env node (v3.0 protocol)
    BREAKING CHANGE: mesh_protocol.h v3.0 — gateway and all nodes must be
    reflashed together. Old MSG_SENSOR_DATA format is not backward compatible.
    Protocol (mesh_protocol.h v3.0)
    - Replaced hardcoded temperature/pressure fields in MsgSensorData with a
    generic SensorReading[] array (id + value pairs)
    - Added MSG_SENSOR_SCHEMA_GET and MSG_SENSOR_SCHEMA message types
2026-03-13 - Simplified the README.md file for non-developers. Makes the project more accessible to a wider audience. - Added a CONTRIBUTING.md file to provide guidelines for contributing to the project.
2026-03-13 feat(web-ui): improve ESP32-S3 Gateway Web Interface structure and asset handling
    - Major Improvements:
    * Fonts are now served locally from device flash instead of being fetched from external CDN sources.
    * Improves reliability in offline environments.
    * Reduces external dependencies.
    * Ensures consistent UI rendering without network latency.
    * Replaced inline SVG icons with dedicated external SVG icon files.
2026-03-14 feat: Added ESP32-S3 Gateway ARGB status LED control
    Features:
    - Added toggle in Web Interface Settings page to enable/disable gateway ARGB LED
    - Implemented WebSocket command for LED control
    - Added gw_led_enabled field to meta JSON for UI synchronization
    - Persist LED state in NVS so it survives gateway reboot
    - UI toggle now reflects actual gateway state on page load
2026-03-15 feat: add actuator node support, relay firmware, and mesh/dashboard updates
    - add ESP32 actuator node support across gateway, protocol, and web interface
    - add actuator message definitions and bump mesh_protocol.h to v3.1.0
    - add NODE_HYBRID for future hybrid sensor-actuator nodes
    - update gateway firmware and bump main.cpp to v1.8.2
    - update dashboard logic and bump app.js to v3.6
    - add ESP32 relay actuator node firmware and bump to v1.0.1
2026-03-17 feat: Relay Label Support - Added per relay label set functionality via Web Interface for ESP32 Actuator Nodes. - Relay Label set/assignment is completely handled by the Web Interface and the Gateway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
2026-03-17 feat(relay-node): add TTP224 touch control for relays with gateway state sync
2026-03-18 feat(gateway): add web-based OTA firmware update system
    - add Gateway OTA firmware upload flow in the web interface
    - add real-time OTA upload progress, status, and error reporting
    - add backend OTA validation for firmware image type, size, and project match
    - add automatic reboot into updated firmware after successful flash
    - add OTA-capable 8MB partition layout for ESP32-S3 Gateway
    - update OTA UI assets and settings page integration
2026-03-20 feat(ota): add gateway-managed node OTA with ESP32-C3 coprocessor support
    - bump ESP32-S3 gateway firmware from v1.9.0 to v2.0.0
    - introduce ESP32-C3 gateway coprocessor firmware v0.1.0
    - add coproc_ota_protocol.h v1.0.0
    - bump mesh_protocol.h from v3.1.0 to v3.2.0
    - bump web interface app.js from v3.8 to v3.9
    - bump web interface index.html from v3.6 to v3.7
2026-03-20 feat(ota): add hardware config ID validation for gateway and node OTA updates
    - add OTA hardware configuration ID precheck to prevent flashing firmware built
    for incompatible hardware revisions
    - extend node OTA validation to require both node role match and hardware config
    ID match before starting OTA
    - extend gateway OTA validation to require gateway hardware config ID match
    before flashing
2026-03-21 feat(hybrid): add RFID-enabled Hybrid node support across gateway, UI, and OTA
    - bump ESP32-S3 gateway firmware from v2.0.1 to v2.1.0
    - bump ESP32-C3 gateway coprocessor firmware from v0.1.0 to v0.1.1
    - bump mesh_protocol.h from v3.2.1 to v3.3.0
    - bump ESP32 sensor node firmware from v2.1.1 to v2.1.2
    - bump ESP32 relay node firmware from v1.1.1 to v1.2.0
    - bump app.js from v4.0 to v4.1
2026-03-21 feat(ui): polish mobile dashboard UX, RFID toasts, and gateway dialogs
    - bump index.html from v3.7 to v3.8
    - bump app.js from v4.1 to v4.2
    - bump style.css from v3.6 to v3.7
    - bump ESP32-S3 gateway firmware main.cpp from v2.1.0 to v2.1.1
    - add RFID scan toasts for new-card detection and known-card actions
    - improve mobile top bar layout and keep IP/MAC/Ch/Up/Nodes labels visible
2026-03-22 feat(hw): add Gateway v1.0A PCB files and update hardware support
    - bump ESP32-S3 gateway firmware main.cpp from v2.1.1 to v2.1.2
    - bump ESP32 Hybrid Relay Node firmware main.cpp from v0.1.0 to v0.1.1
    - add hardware release files for ESP32 Mesh System Gateway v1.0A under gateway_v1/hardware
    - include KiCad project files, schematic PDFs, and Development_Resources with dev-board pinouts and MCU datasheets
    - add the first gateway PCB as a single-layer, thick-trace, THT-friendly design based on off-the-shelf ESP32-S3 Super Mini and ESP32-C3 Super Mini boards for easy home fabrication
    - update ESP32-S3 <-> ESP32-C3 helper UART routing for the new gateway PCB layout:
2026-03-23 feat(pairing): add max-node warning flow and restore node LED status after unpair
    - bump ESP32-S3 gateway firmware main.cpp from v2.1.2 to v2.1.3
    - bump ESP32 sensor node firmware main.cpp from v2.1.2 to v2.1.3
    - bump ESP32 actuator relay node firmware main.cpp from v1.2.0 to v1.2.1
    - bump ESP32 hybrid relay node firmware main.cpp from v0.1.1 to v0.1.2
    - bump app.js from v4.2 to v4.3
    - add a gateway-side max-node-capacity check for pair requests
2026-03-25 feat(protocol): expand node names to 24 chars and add MAC-suffixed defaults
    - bump ESP32-S3 gateway firmware from v2.1.3 to v2.1.4
    - bump ESP32 sensor node firmware from v2.1.3 to v2.1.4
    - bump ESP32 actuator relay node firmware from v1.2.1 to v1.2.2
    - bump ESP32 hybrid relay node firmware from v0.1.2 to v0.1.3
    - bump mesh_protocol.h from v3.3.0 to v3.3.1
    - increase the shared node-name limit from 15 to 24 visible characters
2026-04-03 feat: improve node discovery, add new gateway PCB variants, and document C3 Super Mini RF fixes
    - polish gateway and node discovery behavior so pairing candidates appear faster and stale "available to pair" entries clear more predictably
    - document the new Gateway v1A-v1D single-layer THT PCB variants for these board combinations:
    - v1A: Seeed Studio XIAO ESP32-S3 + ESP32-C3 Super Mini
    - v1B: Seeed Studio XIAO ESP32-S3 + Seeed Studio XIAO ESP32-C3
    - v1C: Seeed Studio XIAO ESP32-S3 + DFRobot Beetle ESP32-C3
    - v1D: Waveshare ESP32-S3-DevKit-C-N8R8 + ESP32-C3 Super Mini
2026-04-03 feat: add coprocessor web OTA, board-aware validation, and explicit gateway build targets
    - add ESP32-C3 coprocessor OTA firmware update support through the Gateway web interface
    - update the Gateway Firmware Update UI to let users choose the target MCU:
    - Main MCU
    - Coprocessor
    - keep the existing ESP32-S3 main MCU OTA flow intact while adding a dedicated coprocessor OTA path
    - implement UART-based firmware transfer from the ESP32-S3 gateway MCU to the ESP32-C3 coprocessor
2026-04-04 feat: harden gateway OTA coordination between node OTA and coprocessor OTA
    - add mutual-exclusion handling between node OTA and coprocessor OTA flows so both cannot use the ESP32-C3 helper at the same time
    - reject coprocessor firmware update attempts while the coprocessor is busy serving as the node OTA helper AP
    - reject node OTA attempts while the coprocessor is busy with a coprocessor firmware update
    - surface the shared busy message "Coprocessor Busy. Please try after some time." in the web interface
    - disable node OTA controls while the coprocessor is reserved and show helper status as Busy
    - extend gateway firmware update UI handling so the busy state is reflected for both MCU targets
2026-04-05 feat: add gateway offline mode, router failover recovery, and physical reset UX
    - add Gateway Offline Mode hosted on the ESP32-S3 so the dashboard remains reachable without a home router
    - add a dedicated offline AP configuration with separate SSID/password defaults and NVS persistence
    - extend the WiFiManager setup portal with:
    - manual offline mode selection
    - offline AP SSID field
    - offline AP password field
2026-04-06 fix: gracefully unpair connected nodes before gateway factory reset
    - update the ESP32-S3 gateway factory reset flow so connected nodes are explicitly disconnected before the gateway wipes its own state
    - send `MSG_UNPAIR_CMD` to every currently paired node when factory reset is triggered from:
    - the dashboard Factory Reset action
    - the physical factory reset button
    - give nodes time to receive the unpair command before the gateway clears local pairing state and reboots
    - clear the gateway runtime node registry only after the unpair notifications have been sent
2026-04-06 feat: add gateway built-in sensor support and improve Super Mini OTA helper stability
    - add optional gateway built-in room environment sensor support on the ESP32-S3 gateway
    - support compile-time selection of:
    - no built-in sensor
    - BMP280
    - BME280
    - expose built-in sensor data through the gateway dashboard as a dedicated `Gateway Built-in Sensor` card
2026-04-08 feat: add MQTT + Home Assistant discovery across gateway mesh
    - add MQTT bridge support to the gateway firmware and web UI
    - publish Home Assistant MQTT auto-discovery for the gateway,
    built-in sensor, and paired sensor/relay/hybrid nodes
    - route relay, setting, reboot, unpair, and gateway control actions
    through MQTT while keeping Home Assistant and the gateway dashboard
    state in sync
2026-04-12 feat(gateway): auto-detect built-in BMP280/BME280 sensor and simplify config
    - add clearer built-in sensor probe and diagnosis logs for gateway SPI sensor detection
    - auto-detect whether the connected built-in sensor is BMP280 or BME280 at runtime
    and publish/show the correct sensor model and readings accordingly
    - remove the old manual gateway built-in sensor type selection logic from firmware
    and replace it with a simple built-in sensor enable flag
    - align gateway dashboard sensor UI with runtime sensor auto-detection
